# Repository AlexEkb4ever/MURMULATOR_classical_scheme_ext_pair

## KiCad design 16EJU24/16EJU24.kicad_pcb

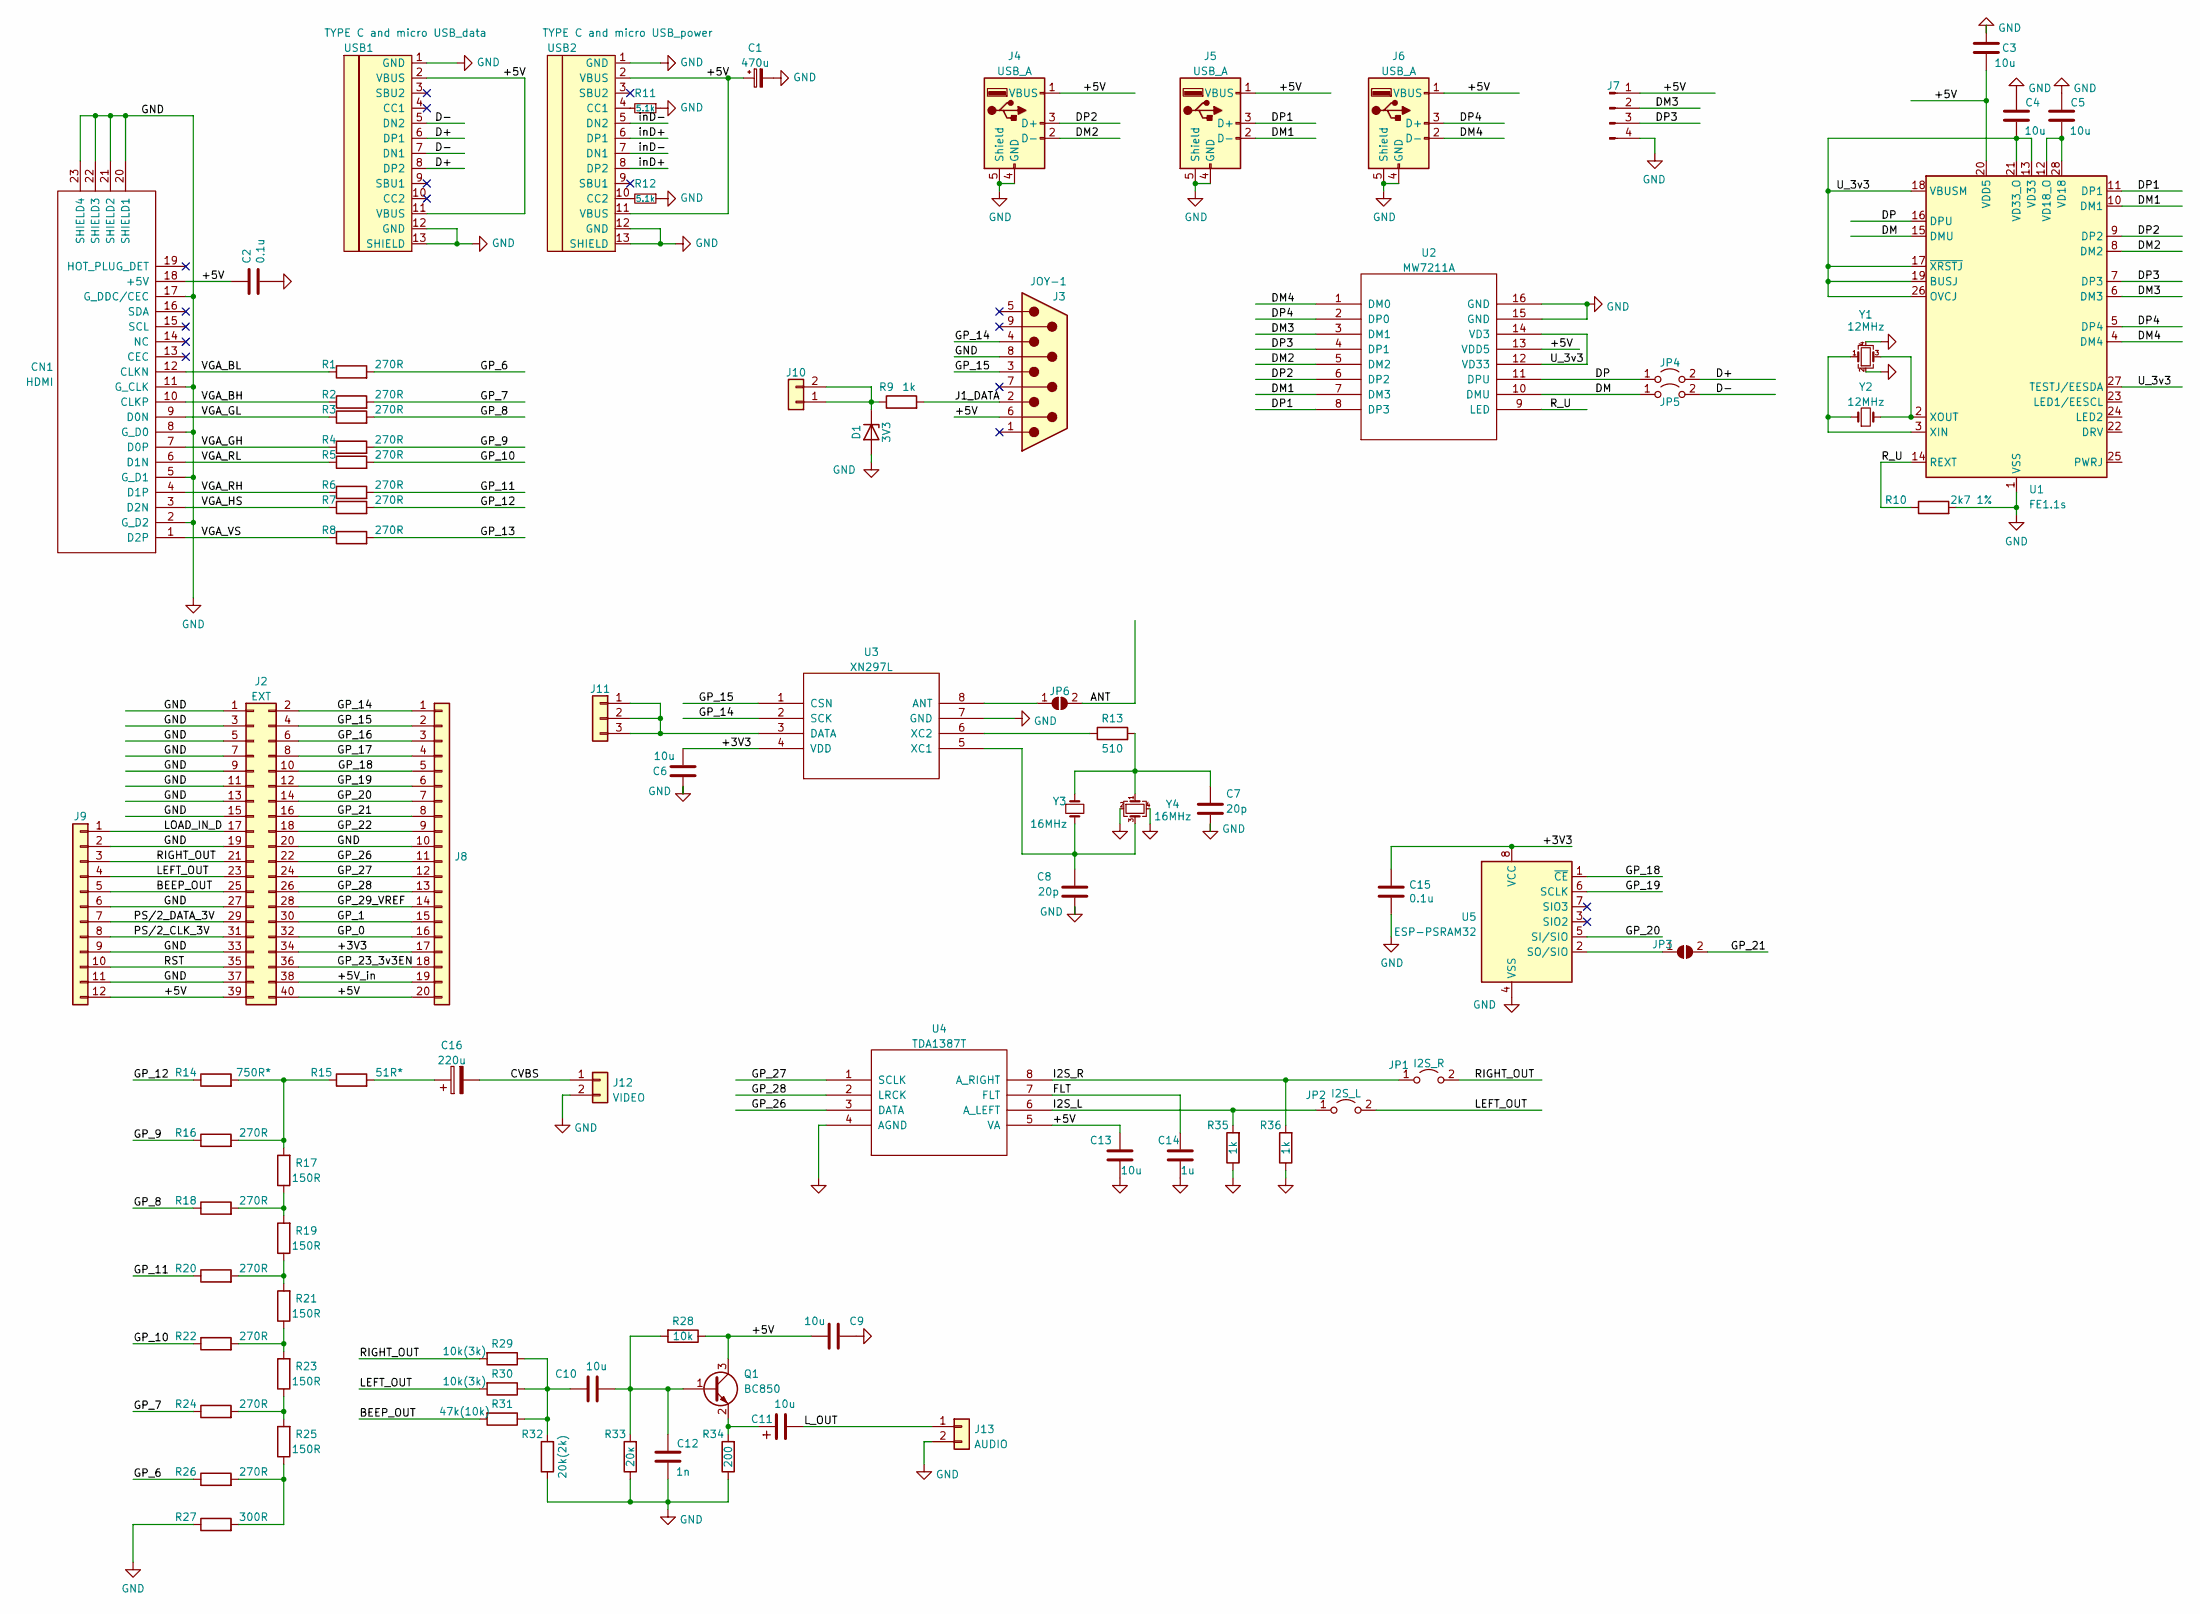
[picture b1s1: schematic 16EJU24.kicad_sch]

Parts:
C1: 470u; CP_Radial_D5.0mm_P2.50mm
C2: 0.1u; R_0805_PLUS
C3, C4, C5, C6, C9, C10, C13: 10u; C_0805_2012Metric_Pad1.18x1.45mm_HandSolder
C7, C8: 20p; C_0805_2012Metric_Pad1.18x1.45mm_HandSolder
C11: 10u; CP_Radial_D5.0mm_P2.50mm
C12: 1n; C_0805_2012Metric_Pad1.18x1.45mm_HandSolder
C14: 1u; C_0805_2012Metric_Pad1.18x1.45mm_HandSolder
C15: 0.1u; C_0805_2012Metric_Pad1.18x1.45mm_HandSolder
C16: 220u; CP_Radial_D5.0mm_P2.50mm
CN1: HDMI
D1: 3V3; R_0805_PLUS
J2: EXT; PinHeader_2x20_P2.54mm_Vertical
J3: JOY-1; DSUB-9_Male_EdgeMount_P2.77mm
J4, J5, J6: USB_A; USB_A_CONNFLY_DS1095-WNR0
J7: Conn_01x04_Male; PinHeader_1x04_P2.54mm_Vertical
J8: Conn_01x20; PinHeader_1x20_P2.54mm_Vertical
J9: Conn_01x12; PinHeader_1x12_P2.54mm_Vertical
J10: Conn_01x02; PinHeader_1x02_P2.54mm_Vertical
J11: Conn_01x03; PinHeader_1x03_P2.54mm_Vertical
J12: VIDEO; AV_MOD_III-8.4-5
J13: AUDIO; AV_MOD_III-8.4-5
JP1: I2S_R; PinHeader_1x02_P2.54mm_Vertical
JP2: I2S_L; PinHeader_1x02_P2.54mm_Vertical
JP3: B_J; SolderJumper-2_P1.3mm_Open_RoundedPad1.0x1.5mm
JP4, JP5: Jumper_2_Open; PinHeader_1x02_P2.54mm_Vertical
JP6: SolderJumper_2_Open; SolderJumper-2_P1.3mm_Open_RoundedPad1.0x1.5mm
Q1: BC850; SOT-23
R1, R2, R3, R4, R5, R6, R7, R8: 270R; R_0805_PLUS
R9, R35, R36: 1k; R_0805_2012Metric_Pad1.20x1.40mm_HandSolder
R10: 2k7 1%; R_0805_2012Metric_Pad1.20x1.40mm_HandSolder
R11, R12: 5.1k; R_0805_2012Metric_Pad1.20x1.40mm_HandSolder
R13: 510; R_0805_2012Metric_Pad1.20x1.40mm_HandSolder
R14: 750R*; R_0805_2012Metric_Pad1.20x1.40mm_HandSolder
R15: 51R*; R_0805_2012Metric_Pad1.20x1.40mm_HandSolder
R16, R18, R20, R22, R24, R26: 270R; R_0805_2012Metric_Pad1.20x1.40mm_HandSolder
R17, R19, R21, R23, R25: 150R; R_0805_2012Metric_Pad1.20x1.40mm_HandSolder
R27: 300R; R_0805_2012Metric_Pad1.20x1.40mm_HandSolder
R28: 10k; R_0805_2012Metric_Pad1.20x1.40mm_HandSolder
R29, R30: 10k(3k); R_0805_2012Metric_Pad1.20x1.40mm_HandSolder
R31: 47k(10k); R_0805_2012Metric_Pad1.20x1.40mm_HandSolder
R32: 20k(2k); R_0805_2012Metric_Pad1.20x1.40mm_HandSolder
R33: 20к; R_0805_2012Metric_Pad1.20x1.40mm_HandSolder
R34: 200; R_0805_2012Metric_Pad1.20x1.40mm_HandSolder
U1: FE1.1s; SSOP-28_3.9x9.9mm_P0.635mm
U2: MW7211A; SO-16_5.3x10.2mm_P1.27mm
U3: XN297L; SO-8_5.3x6.2mm_P1.27mm
U4: TDA1387T; SO-8_5.3x6.2mm_P1.27mm
U5: ESP-PSRAM32; SO-8_5.3x6.2mm_P1.27mm
USB1: TYPE C and micro USB_data; USB-TYPEC_MICRO_USBII; LCSC C165948
USB2: TYPE C and micro USB_power; USB-TYPEC_MICRO_USBII; LCSC C165948
Y1: 12MHz; Crystal_SMD_0603-4Pin_6.0x3.5mm
Y2: 12MHz; Crystal_HC49-4H_Vertical
Y3: 16MHz; Crystal_HC49-4H_Vertical
Y4: 16MHz; Crystal_SMD_0603-4Pin_6.0x3.5mm

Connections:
/+3V3: C6.2, C15.1, J2.34, J8.17, U3.4 (VDD), U5.8 (VCC); also elsewhere on the board
/+5V: C1.1, C2.1, C3.2, C9.2, C13.2, CN1.18 (+5V), J2.39, J2.40, J3.6, J4.1 (VBUS), J5.1 (VBUS), J6.1 (VBUS), J7.1, J8.20, J9.12, Q1.3 (C), R28.1, U1.20 (VDD5), U2.13 (VDD5), U4.5 (VA), USB1.2 (VBUS), USB1.11 (VBUS), USB2.2 (VBUS), USB2.11 (VBUS); also elsewhere on the board
/+5V_in: J2.38, J8.19
/ANT: JP6.2 (B)
/BEEP_OUT: J2.25, J9.5, R31.2
/CVBS: C16.2, J12.1
/D+: JP4.2 (B), USB1.6 (DP1), USB1.8 (DP2); also elsewhere on the board
/D-: JP5.2 (B), USB1.5 (DN2), USB1.7 (DN1); also elsewhere on the board
/DM: JP5.1 (A), U1.15 (DMU), U2.10 (DMU)
/DM1: J5.2 (D-), U1.10 (DM1), U2.7 (DM3)
/DM2: J4.2 (D-), U1.8 (DM2), U2.5 (DM2)
/DM3: J7.2, U1.6 (DM3), U2.3 (DM1)
/DM4: J6.2 (D-), U1.4 (DM4), U2.1 (DM0)
/DP: JP4.1 (A), U1.16 (DPU), U2.11 (DPU)
/DP1: J5.3 (D+), U1.11 (DP1), U2.8 (DP3)
/DP2: J4.3 (D+), U1.9 (DP2), U2.6 (DP2)
/DP3: J7.3, U1.7 (DP3), U2.4 (DP1)
/DP4: J6.3 (D+), U1.5 (DP4), U2.2 (DP0)
/FLT: C14.2, U4.7 (FLT)
/GP_0: J2.32, J8.16
/GP_1: J2.30, J8.15
/GP_6: R1.2, R26.1
/GP_7: R2.2, R24.1
/GP_8: R3.2, R18.1
/GP_9: R4.2, R16.1
/GP_10: R5.2, R22.1
/GP_11: R6.2, R20.1
/GP_12: R7.2, R14.1
/GP_13: R8.2
/GP_14: J2.2, J3.4, J8.1, U3.2 (SCK); also elsewhere on the board
/GP_15: J2.4, J3.3, J8.2, U3.1 (CSN); also elsewhere on the board
/GP_16: J2.6, J8.3
/GP_17: J2.8, J8.4
/GP_18: J2.10, J8.5, U5.1 (~CE)
/GP_19: J2.12, J8.6, U5.6 (SCLK)
/GP_20: J2.14, J8.7, U5.5 (SI/SIO)
/GP_21: J2.16, J8.8, JP3.2 (B)
/GP_22: J2.18, J8.9
/GP_23_3v3EN: J2.36, J8.18
/GP_26: J2.22, J8.11, U4.3 (DATA)
/GP_27: J2.24, J8.12, U4.1 (SCLK)
/GP_28: J2.26, J8.13, U4.2 (LRCK)
/GP_29_VREF: J2.28, J8.14
/I2S_L: JP2.1 (A), R35.2, U4.6 (A_LEFT)
/I2S_R: JP1.1 (A), R36.2, U4.8 (A_RIGHT)
/J1_DATA: J3.2, R9.2
/LEFT_OUT: J2.23, J9.4, JP2.2 (B), R30.2
/LOAD_IN_D: J2.17, J9.1
/L_OUT: C11.2, J13.1
/PS/2_CLK_3V: J2.31, J9.8
/PS/2_DATA_3V: J2.29, J9.7
/RIGHT_OUT: J2.21, J9.3, JP1.2 (B), R29.2
/RST: J2.35, J9.10
/R_U: R10.1, U1.14 (REXT), U2.9 (LED)
/U_3v3: C4.2, U1.13 (VD33), U1.17 (~XRSTJ), U1.18 (VBUSM), U1.19 (BUSJ), U1.21 (VD33_O), U1.26 (OVCJ), U1.27 (TESTJ/EESDA), U2.12 (VD33), U2.14 (VD3)
/VGA_BH: CN1.10 (CLKP), R2.1
/VGA_BL: CN1.12 (CLKN), R1.1
/VGA_GH: CN1.7 (D0P), R4.1
/VGA_GL: CN1.9 (D0N), R3.1
/VGA_HS: CN1.3 (D2N), R7.1
/VGA_RH: CN1.4 (D1P), R6.1
/VGA_RL: CN1.6 (D1N), R5.1
/VGA_VS: CN1.1 (D2P), R8.1
/inD+: USB2.6 (DP1), USB2.8 (DP2); also elsewhere on the board
/inD-: USB2.5 (DN2), USB2.7 (DN1); also elsewhere on the board
GND: C1.2, C2.2, C3.1, C4.1, C5.1, C6.1, C7.1, C8.1, C9.1, C12.2, C13.1, C14.1, C15.2, CN1.2 (G_D2), CN1.5 (G_D1), CN1.8 (G_D0), CN1.11 (G_CLK), CN1.17 (G_DDC/CEC), CN1.20 (SHIELD1), CN1.21 (SHIELD2), CN1.22 (SHIELD3), CN1.23 (SHIELD4), D1.2 (A), J2.1, J2.3, J2.5, J2.7, J2.9, J2.11, J2.13, J2.15, J2.19, J2.20, J2.27, J2.33, J2.37, J3.8, J4.4 (GND), J4.5 (Shield), J5.4 (GND), J5.5 (Shield), J6.4 (GND), J6.5 (Shield), J7.4, J8.10, J9.2, J9.6, J9.9, J9.11, J12.2, J13.2, R10.2, R11.1, R12.1, R27.1, R32.1, R33.1, R34.1, R35.1, R36.1, U1.1 (VSS), U2.15 (GND), U2.16 (GND), U3.7 (GND), U4.4 (AGND), U5.4 (VSS), USB1.1 (GND), USB1.12 (GND), USB1.13 (SHIELD), USB2.1 (GND), USB2.12 (GND), USB2.13 (SHIELD), Y1.2, Y1.4, Y4.2, Y4.4; also elsewhere on the board
unnamed: C5.2, U1.12 (VD18_O), U1.28 (VD18)
unnamed: C7.2, R13.2, Y3.1, Y4.1
unnamed: C8.2, U3.5 (XC1), Y3.2, Y4.3
unnamed: C10.1, R29.1, R30.1, R31.1, R32.2
unnamed: C10.2, C12.1, Q1.1 (B), R28.2, R33.2
unnamed: C11.1, Q1.2 (E), R34.2
unnamed: C16.1, R15.2
unnamed: D1.1 (K), J10.1, J10.2, R9.1
unnamed: J11.1, J11.2, J11.3, U3.3 (DATA)
unnamed: JP3.1 (A), U5.2 (SO/SIO)
unnamed: JP6.1 (A), U3.8 (ANT)
unnamed: R11.2, USB2.4 (CC1)
unnamed: R12.2, USB2.10 (CC2)
unnamed: R13.1, U3.6 (XC2)
unnamed: R14.2, R15.1, R16.2, R17.2
unnamed: R17.1, R18.2, R19.2
unnamed: R19.1, R20.2, R21.2
unnamed: R21.1, R22.2, R23.2
unnamed: R23.1, R24.2, R25.2
unnamed: R25.1, R26.2, R27.2
unnamed: U1.2 (XOUT), Y1.3, Y2.2
unnamed: U1.3 (XIN), Y1.1, Y2.1

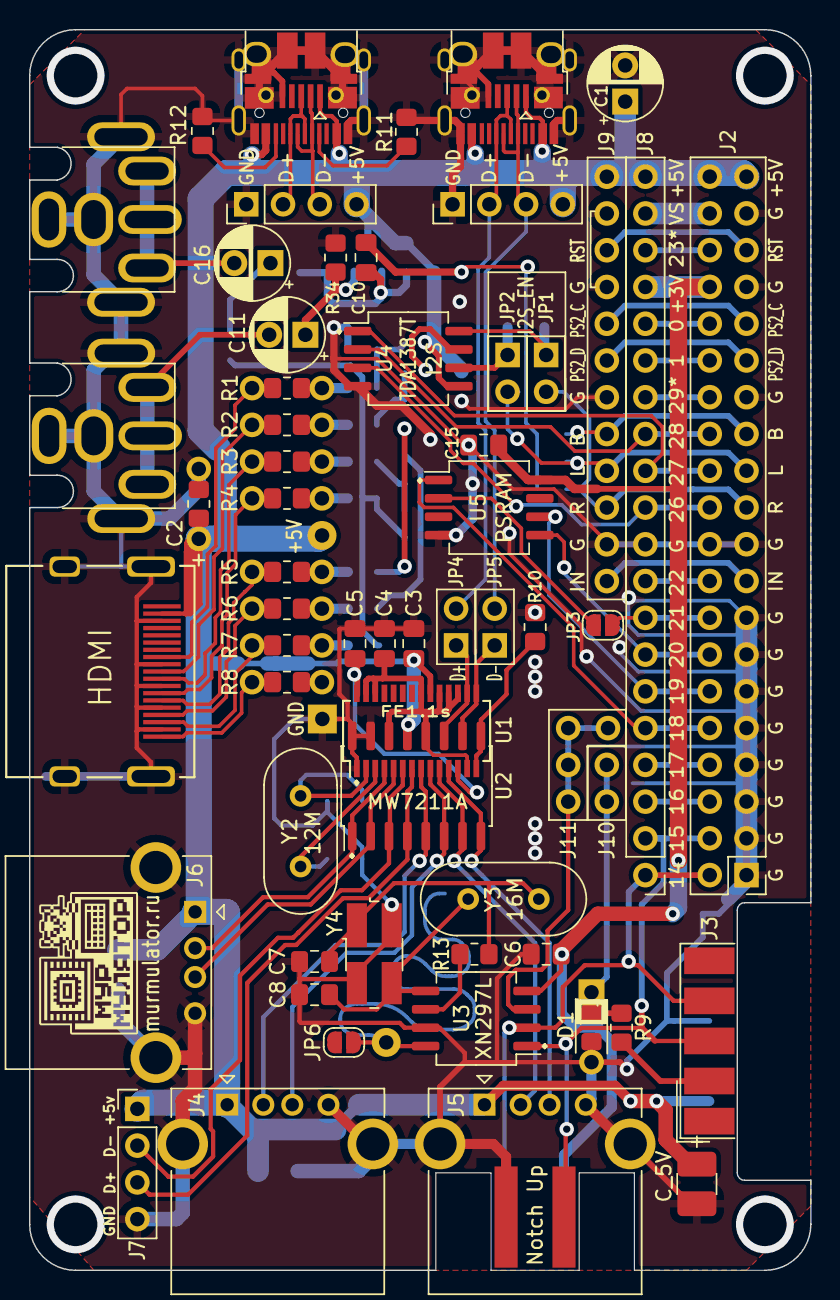
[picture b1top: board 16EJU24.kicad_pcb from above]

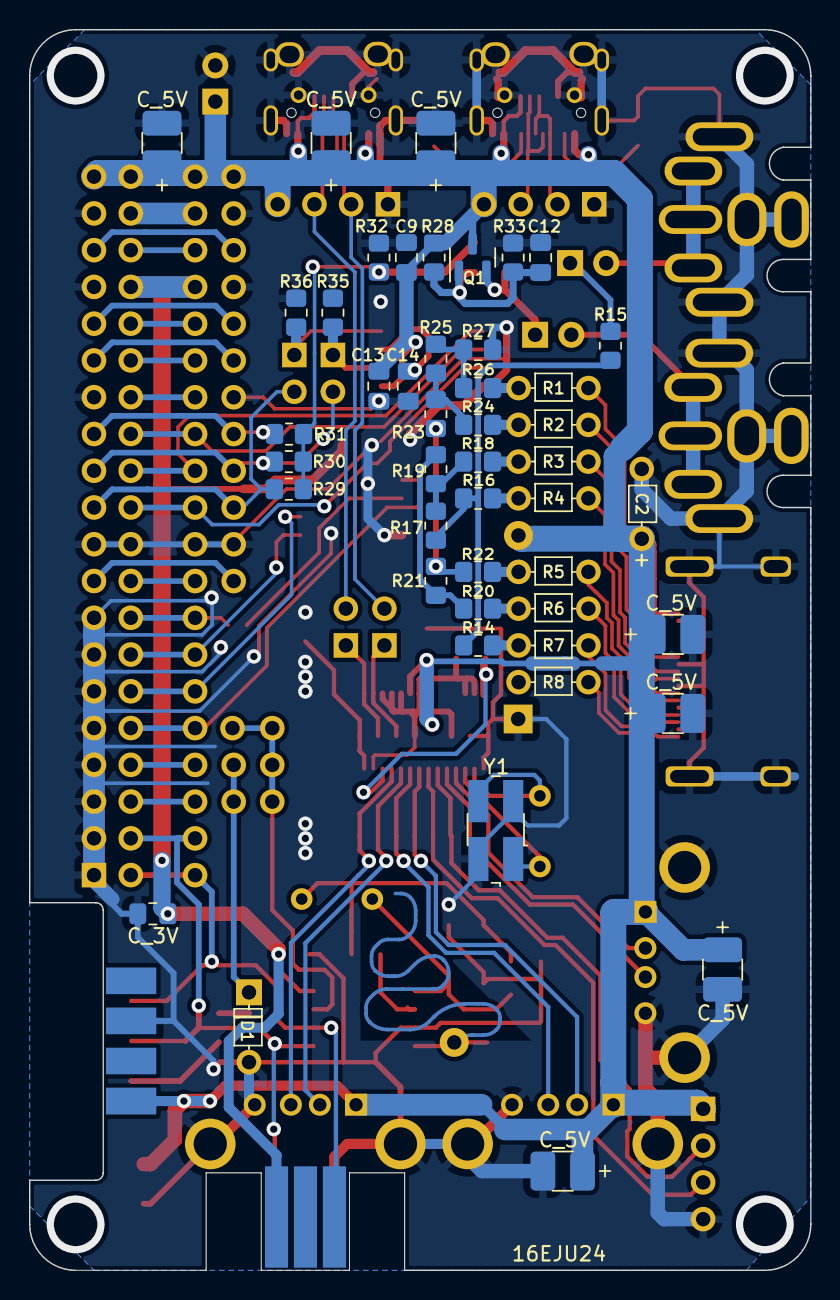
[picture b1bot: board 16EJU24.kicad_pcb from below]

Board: 2 copper layers, 54.0 x 85.7 mm, 96 parts (37 on the bottom side), 86 nets.

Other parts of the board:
C_3V: 10u; C_0805_2012Metric_Pad1.18x1.45mm_HandSolder
C_5V, C_5V#2, C_5V#3, C_5V#4, C_5V#5, C_5V#6, C_5V#7, C_5V#8: C_1210_3225Metric_Pad1.33x2.70mm_HandSolder
USB: PinHeader_1x04_P2.54mm_Vertical
USB#2: PinHeader_1x04_P2.54mm_Vertical
i2c: Crystal_SMD_0603-4Pin_6.0x3.5mm

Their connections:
/+3V3: C_3V.2, i2c.3; also elsewhere on the board
/+5V: C_5V.1, C_5V#2.1, C_5V#3.1, C_5V#4.1, C_5V#5.1, C_5V#6.1, C_5V#7.1, C_5V#8.1, USB.4, USB#2.4; also elsewhere on the board
/D+: USB#2.2; also elsewhere on the board
/D-: USB#2.3; also elsewhere on the board
/GP_14: i2c.1; also elsewhere on the board
/GP_15: i2c.4; also elsewhere on the board
/inD+: USB.2; also elsewhere on the board
/inD-: USB.3; also elsewhere on the board
GND: C_3V.1, C_5V.2, C_5V#2.2, C_5V#3.2, C_5V#4.2, C_5V#5.2, C_5V#6.2, C_5V#7.2, C_5V#8.2, USB.1, USB#2.1, i2c.6; also elsewhere on the board

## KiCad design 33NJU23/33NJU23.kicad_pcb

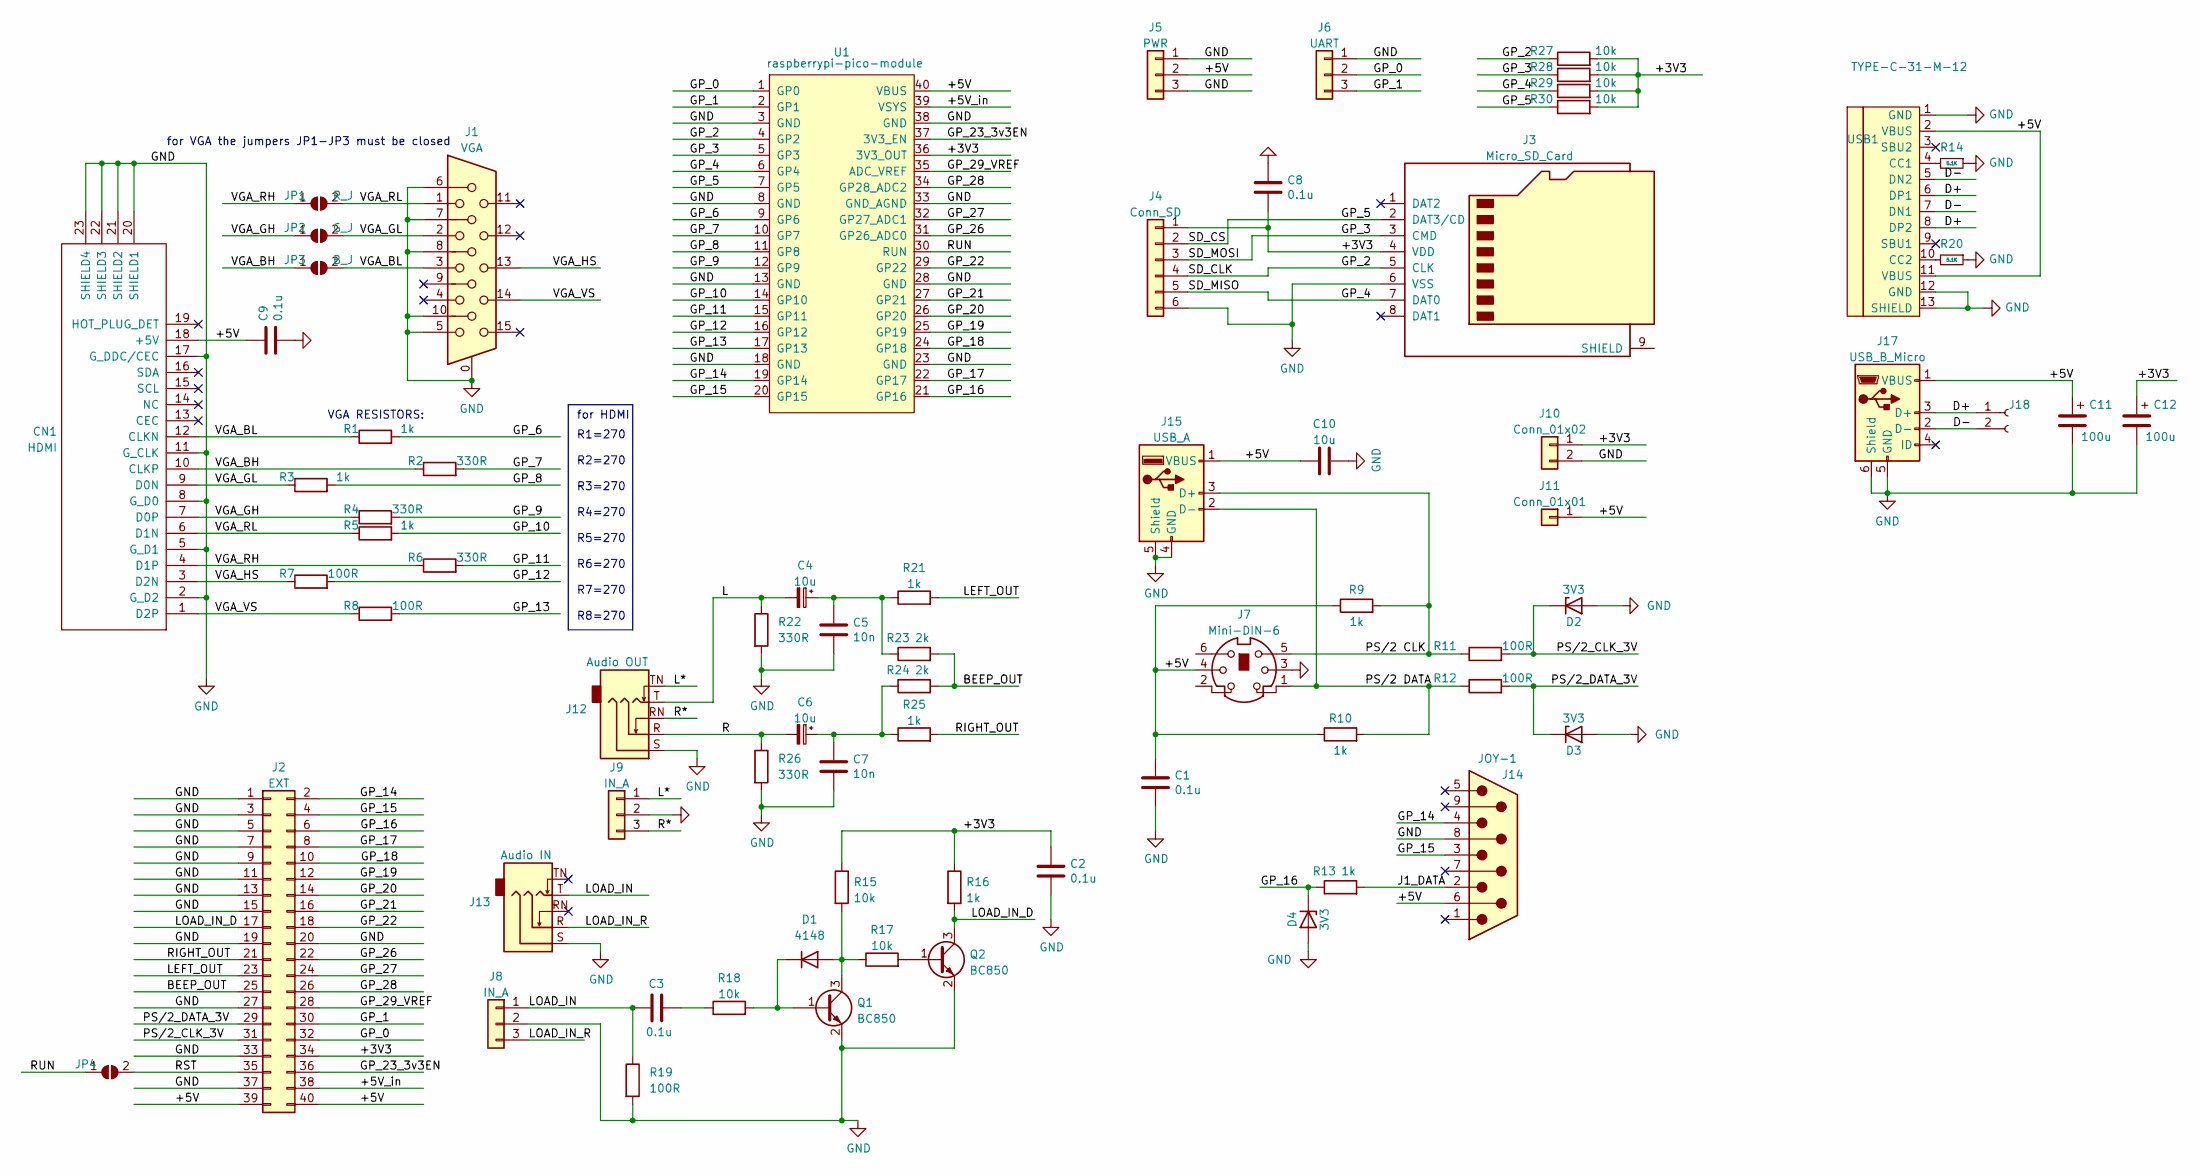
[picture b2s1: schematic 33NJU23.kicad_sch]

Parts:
C1, C2, C3, C8, C9: 0.1u; R_0805_PLUS
C4, C6: 10u; CP_Radial_D5.0mm_P2.50mm
C5, C7: 10n; R_0805_PLUS
C10: 10u; C_0805_2012Metric_Pad1.18x1.45mm_HandSolder
C11, C12: 100u; CP_EIA-7132-28_AVX-C_Pad2.72x3.50mm_HandSolder
CN1: HDMI
D1: 4148; R_0805_PLUS
D2, D3, D4: 3V3; R_0805_PLUS
J1: VGA; DSUB-15-HD_Female_Horizontal_P2.29x1.98mm_EdgePinOffset3.03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
J2: EXT; PinHeader_2x20_P2.54mm_Vertical
J3: Micro_SD_Card; GCT-MEM2055-00-190-01-A
J4: Conn_SD; PinSocket_1x06_P2.54mm_Vertical
J5: PWR; PinHeader_1x03_P2.54mm_Vertical
J6: UART; PinHeader_1x03_P2.54mm_Vertical
J7: Mini-DIN-6; Connector_Mini-DIN_Female_6Pin_2rows
J8, J9: IN_A; PinHeader_1x03_P2.54mm_Vertical
J10: Conn_01x02; PinHeader_1x02_P2.54mm_Vertical
J11: Conn_01x01; PinHeader_1x01_P2.54mm_Vertical
J12: Audio OUT; Jack_3.5mm_CUI_SJ1-3535NG_Horizontal
J13: Audio IN; Jack_3.5mm_CUI_SJ1-3535NG_Horizontal
J14: JOY-1; DSUB-9_Male_EdgeMount_P2.77mm
J15: USB_A; USB_A_CONNFLY_DS1095-WNR0
J17: USB_B_Micro; USB_Micro-B_Amphenol
J18: Conn_01x02_Female; PinHeader_1x02_P2.54mm_Vertical
JP1: R_J; SolderJumper-2_P1.3mm_Open_RoundedPad1.0x1.5mm
JP2: G_J; SolderJumper-2_P1.3mm_Open_RoundedPad1.0x1.5mm
JP3: B_J; SolderJumper-2_P1.3mm_Open_RoundedPad1.0x1.5mm
JP4: JRST; SolderJumper-2_P1.3mm_Open_RoundedPad1.0x1.5mm
Q1, Q2: BC850; SOT-23_PLUS2
R1, R3, R5, R9, R10, R13, R16, R21, R25: 1k; R_0805_PLUS
R2, R4, R6, R22, R26: 330R; R_0805_PLUS
R7, R8, R11, R12, R19: 100R; R_0805_PLUS
R14, R20: 5.1K; R_0805_2012Metric_Pad1.20x1.40mm_HandSolder
R15, R17, R18: 10k; R_0805_PLUS
R23, R24: 2k; R_0805_PLUS
R27, R28, R29, R30: 10k; R_0805_2012Metric_Pad1.20x1.40mm_HandSolder
U1: raspberrypi-pico-module; Raspberry_Pi_Pico_SMT_THT_MOD_2
USB1: TYPE-C-31-M-12; USB-TYPE-C-31-M-12_lib2; LCSC C165948

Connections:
/+3V3: C2.1, C8.2, C12.1, J2.34, J3.4 (VDD), J4.1, J10.1, R15.1, R16.1, R27.2, R28.2, R29.2, R30.2, U1.36 (3V3_OUT)
/+5V: C1.1, C9.1, C10.1, C11.1, CN1.18 (+5V), J2.39, J2.40, J5.2, J7.4, J11.1, J14.6, J15.1 (VBUS), J17.1 (VBUS), R9.1, R10.1, U1.40 (VBUS), USB1.2 (VBUS), USB1.11 (VBUS)
/+5V_in: J2.38, U1.39 (VSYS)
/BEEP_OUT: J2.25, R23.2, R24.2
/D+: J17.3 (D+), J18.1, USB1.6 (DP1), USB1.8 (DP2)
/D-: J17.2 (D-), J18.2, USB1.5 (DN2), USB1.7 (DN1)
/GP_0: J2.32, J6.2, U1.1 (GP0)
/GP_1: J2.30, J6.3, U1.2 (GP1)
/GP_2: J3.5 (CLK), J4.4, R27.1, U1.4 (GP2)
/GP_3: J3.3 (CMD), J4.3, R28.1, U1.5 (GP3)
/GP_4: J3.7 (DAT0), J4.5, R29.1, U1.6 (GP4)
/GP_5: J3.2 (DAT3/CD), J4.2, R30.1, U1.7 (GP5)
/GP_6: R1.2, U1.9 (GP6)
/GP_7: R2.2, U1.10 (GP7)
/GP_8: R3.2, U1.11 (GP8)
/GP_9: R4.2, U1.12 (GP9)
/GP_10: R5.2, U1.14 (GP10)
/GP_11: R6.2, U1.15 (GP11)
/GP_12: R7.2, U1.16 (GP12)
/GP_13: R8.2, U1.17 (GP13)
/GP_14: J2.2, J14.4, U1.19 (GP14)
/GP_15: J2.4, J14.3, U1.20 (GP15)
/GP_16: D4.1 (K), J2.6, R13.1, U1.21 (GP16)
/GP_17: J2.8, U1.22 (GP17)
/GP_18: J2.10, U1.24 (GP18)
/GP_19: J2.12, U1.25 (GP19)
/GP_20: J2.14, U1.26 (GP20)
/GP_21: J2.16, U1.27 (GP21)
/GP_22: J2.18, U1.29 (GP22)
/GP_23_3v3EN: J2.36, U1.37 (3V3_EN)
/GP_26: J2.22, U1.31 (GP26_ADC0)
/GP_27: J2.24, U1.32 (GP27_ADC1)
/GP_28: J2.26, U1.34 (GP28_ADC2)
/GP_29_VREF: J2.28, U1.35 (ADC_VREF)
/J1_DATA: J14.2, R13.2
/L: C4.2, J12.T, R22.1
/L*: J9.1, J12.TN
/LEFT_OUT: J2.23, R21.2
/LOAD_IN: C3.1, J8.1, J13.T, R19.1
/LOAD_IN_D: J2.17, Q2.3 (C), R16.2
/LOAD_IN_R: J8.3, J13.R
/PS/2 CLK: J7.5, J15.3 (D+), R9.2, R11.1
/PS/2 DATA: J7.1, J15.2 (D-), R10.2, R12.1
/PS/2_CLK_3V: D2.1 (K), J2.31, R11.2
/PS/2_DATA_3V: D3.1 (K), J2.29, R12.2
/R: C6.2, J12.R, R26.1
/R*: J9.3, J12.RN
/RIGHT_OUT: J2.21, R25.2
/RST: J2.35, JP4.2 (B)
/RUN: JP4.1 (A), U1.30 (RUN)
/VGA_BH: CN1.10 (CLKP), JP3.1 (A), R2.1
/VGA_BL: CN1.12 (CLKN), J1.3, JP3.2 (B), R1.1
/VGA_GH: CN1.7 (D0P), JP2.1 (A), R4.1
/VGA_GL: CN1.9 (D0N), J1.2, JP2.2 (B), R3.1
/VGA_HS: CN1.3 (D2N), J1.13, R7.1
/VGA_RH: CN1.4 (D1P), JP1.1 (A), R6.1
/VGA_RL: CN1.6 (D1N), J1.1, JP1.2 (B), R5.1
/VGA_VS: CN1.1 (D2P), J1.14, R8.1
GND: C1.2, C2.2, C5.2, C7.2, C8.1, C9.2, C10.2, C11.2, C12.2, CN1.2 (G_D2), CN1.5 (G_D1), CN1.8 (G_D0), CN1.11 (G_CLK), CN1.17 (G_DDC/CEC), CN1.20 (SHIELD1), CN1.21 (SHIELD2), CN1.22 (SHIELD3), CN1.23 (SHIELD4), D2.2 (A), D3.2 (A), D4.2 (A), J1.0, J1.5, J1.6, J1.7, J1.8, J1.10, J2.1, J2.3, J2.5, J2.7, J2.9, J2.11, J2.13, J2.15, J2.19, J2.20, J2.27, J2.33, J2.37, J3.6 (VSS), J4.6, J5.1, J5.3, J6.1, J7.3, J8.2, J9.2, J10.2, J12.S, J13.S, J14.8, J15.4 (GND), J15.5 (Shield), J17.5 (GND), J17.6 (Shield), Q1.2 (E), Q2.2 (E), R14.1, R19.2, R20.1, R22.2, R26.2, U1.3 (GND), U1.8 (GND), U1.13 (GND), U1.18 (GND), U1.23 (GND), U1.28 (GND), U1.33 (GND_AGND), U1.38 (GND), USB1.1 (GND), USB1.12 (GND), USB1.13 (SHIELD)
unnamed: C3.2, R18.1
unnamed: C4.1, C5.1, R21.1, R23.1
unnamed: C6.1, C7.1, R24.1, R25.1
unnamed: D1.1 (K), Q1.1 (B), R18.2
unnamed: D1.2 (A), Q1.3 (C), R15.2, R17.1
unnamed: Q2.1 (B), R17.2
unnamed: R14.2, USB1.4 (CC1)
unnamed: R20.2, USB1.10 (CC2)

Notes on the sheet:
for VGA the jumpers JP1-JP3 must be closed
VGA RESISTORS:
for HDMI
R1=270 R2=270 R3=270 R4=270 R5=270 R6=270 R7=270 R8=270

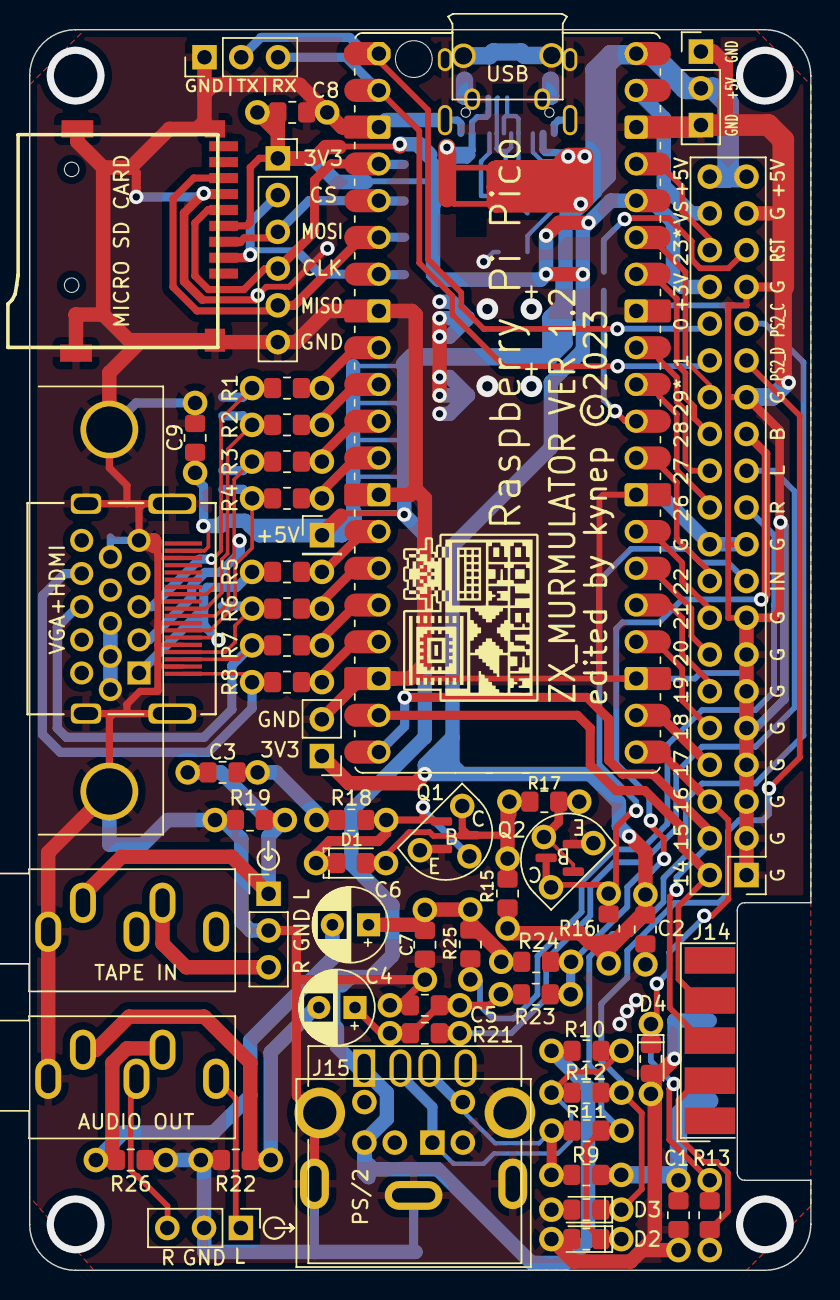
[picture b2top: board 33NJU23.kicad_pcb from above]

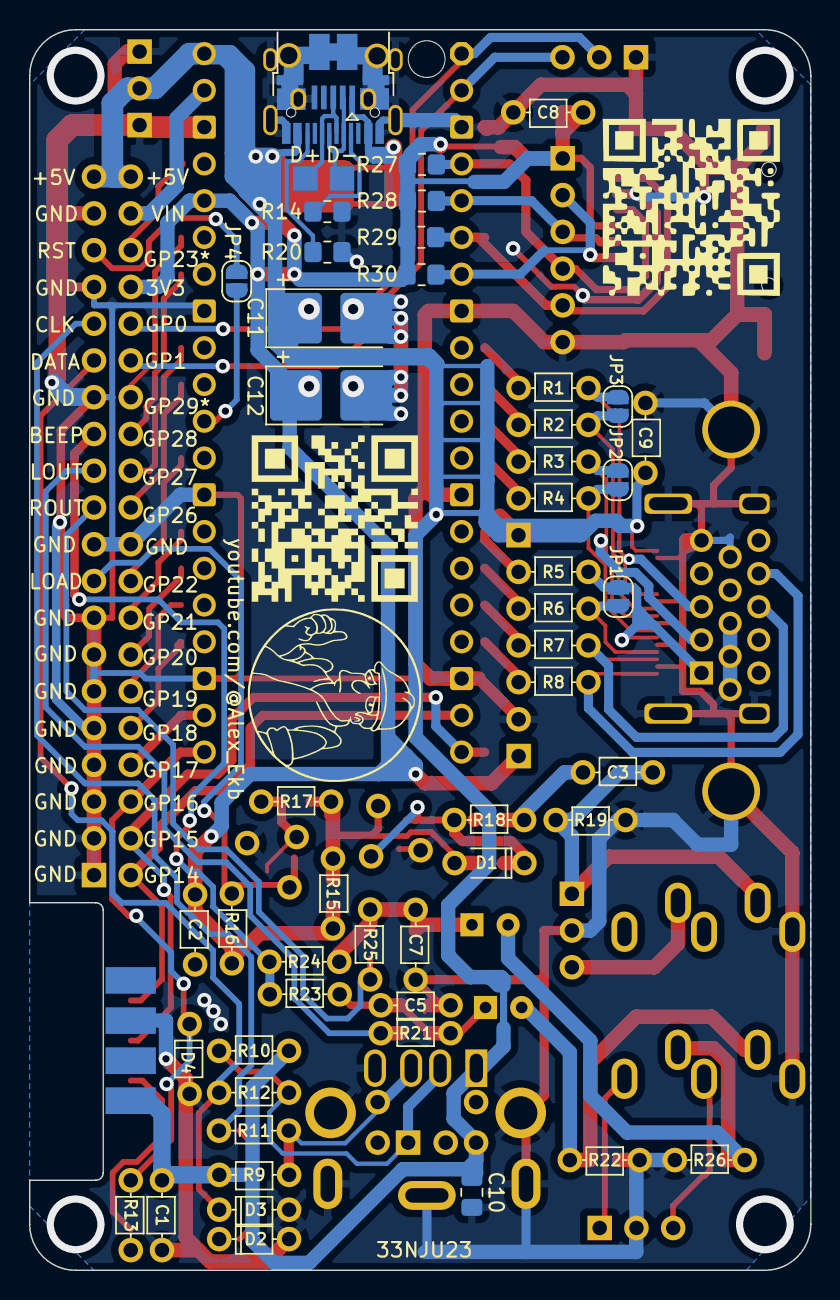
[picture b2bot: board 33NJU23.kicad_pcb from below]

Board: 2 copper layers, 54.0 x 85.7 mm, 72 parts (16 on the bottom side), 67 nets.

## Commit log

2023-08-29 create
2023-09-10 logo
2024-02-09 reload
2024-05-25 16EJU24 create

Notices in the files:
33NJU23/33NJU23.kicad_pcb:
edited by kynep ©2023
